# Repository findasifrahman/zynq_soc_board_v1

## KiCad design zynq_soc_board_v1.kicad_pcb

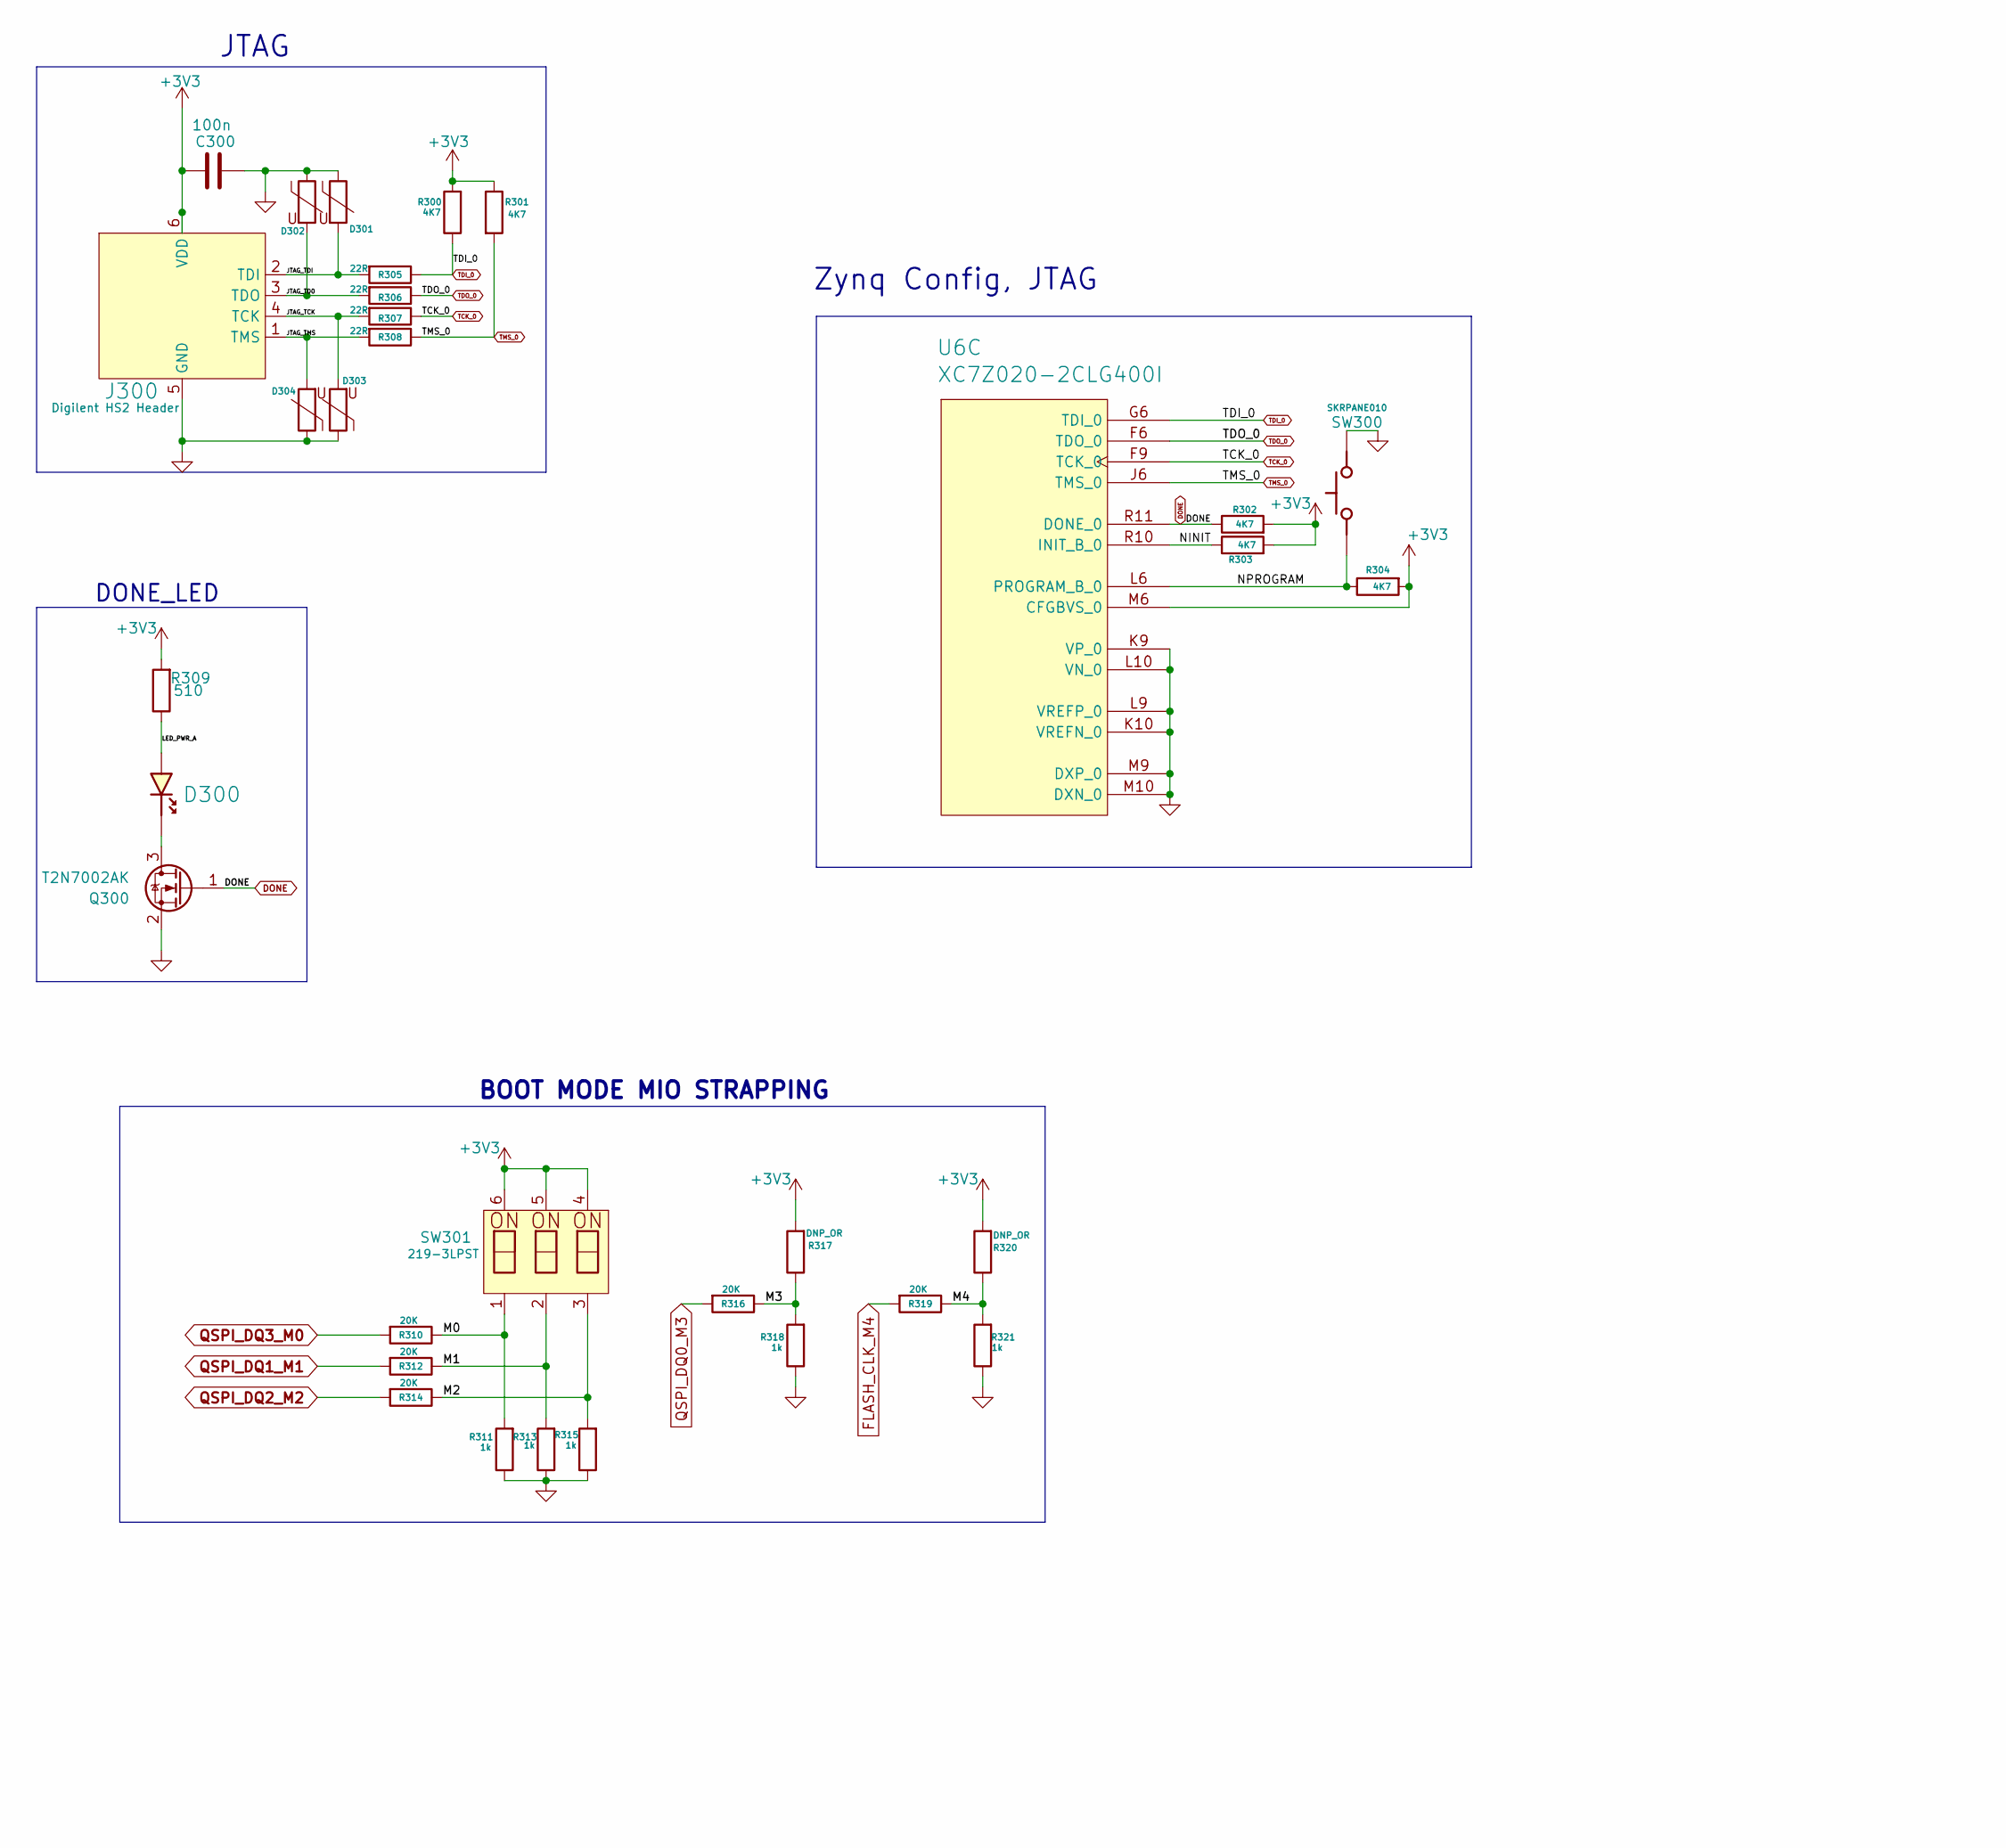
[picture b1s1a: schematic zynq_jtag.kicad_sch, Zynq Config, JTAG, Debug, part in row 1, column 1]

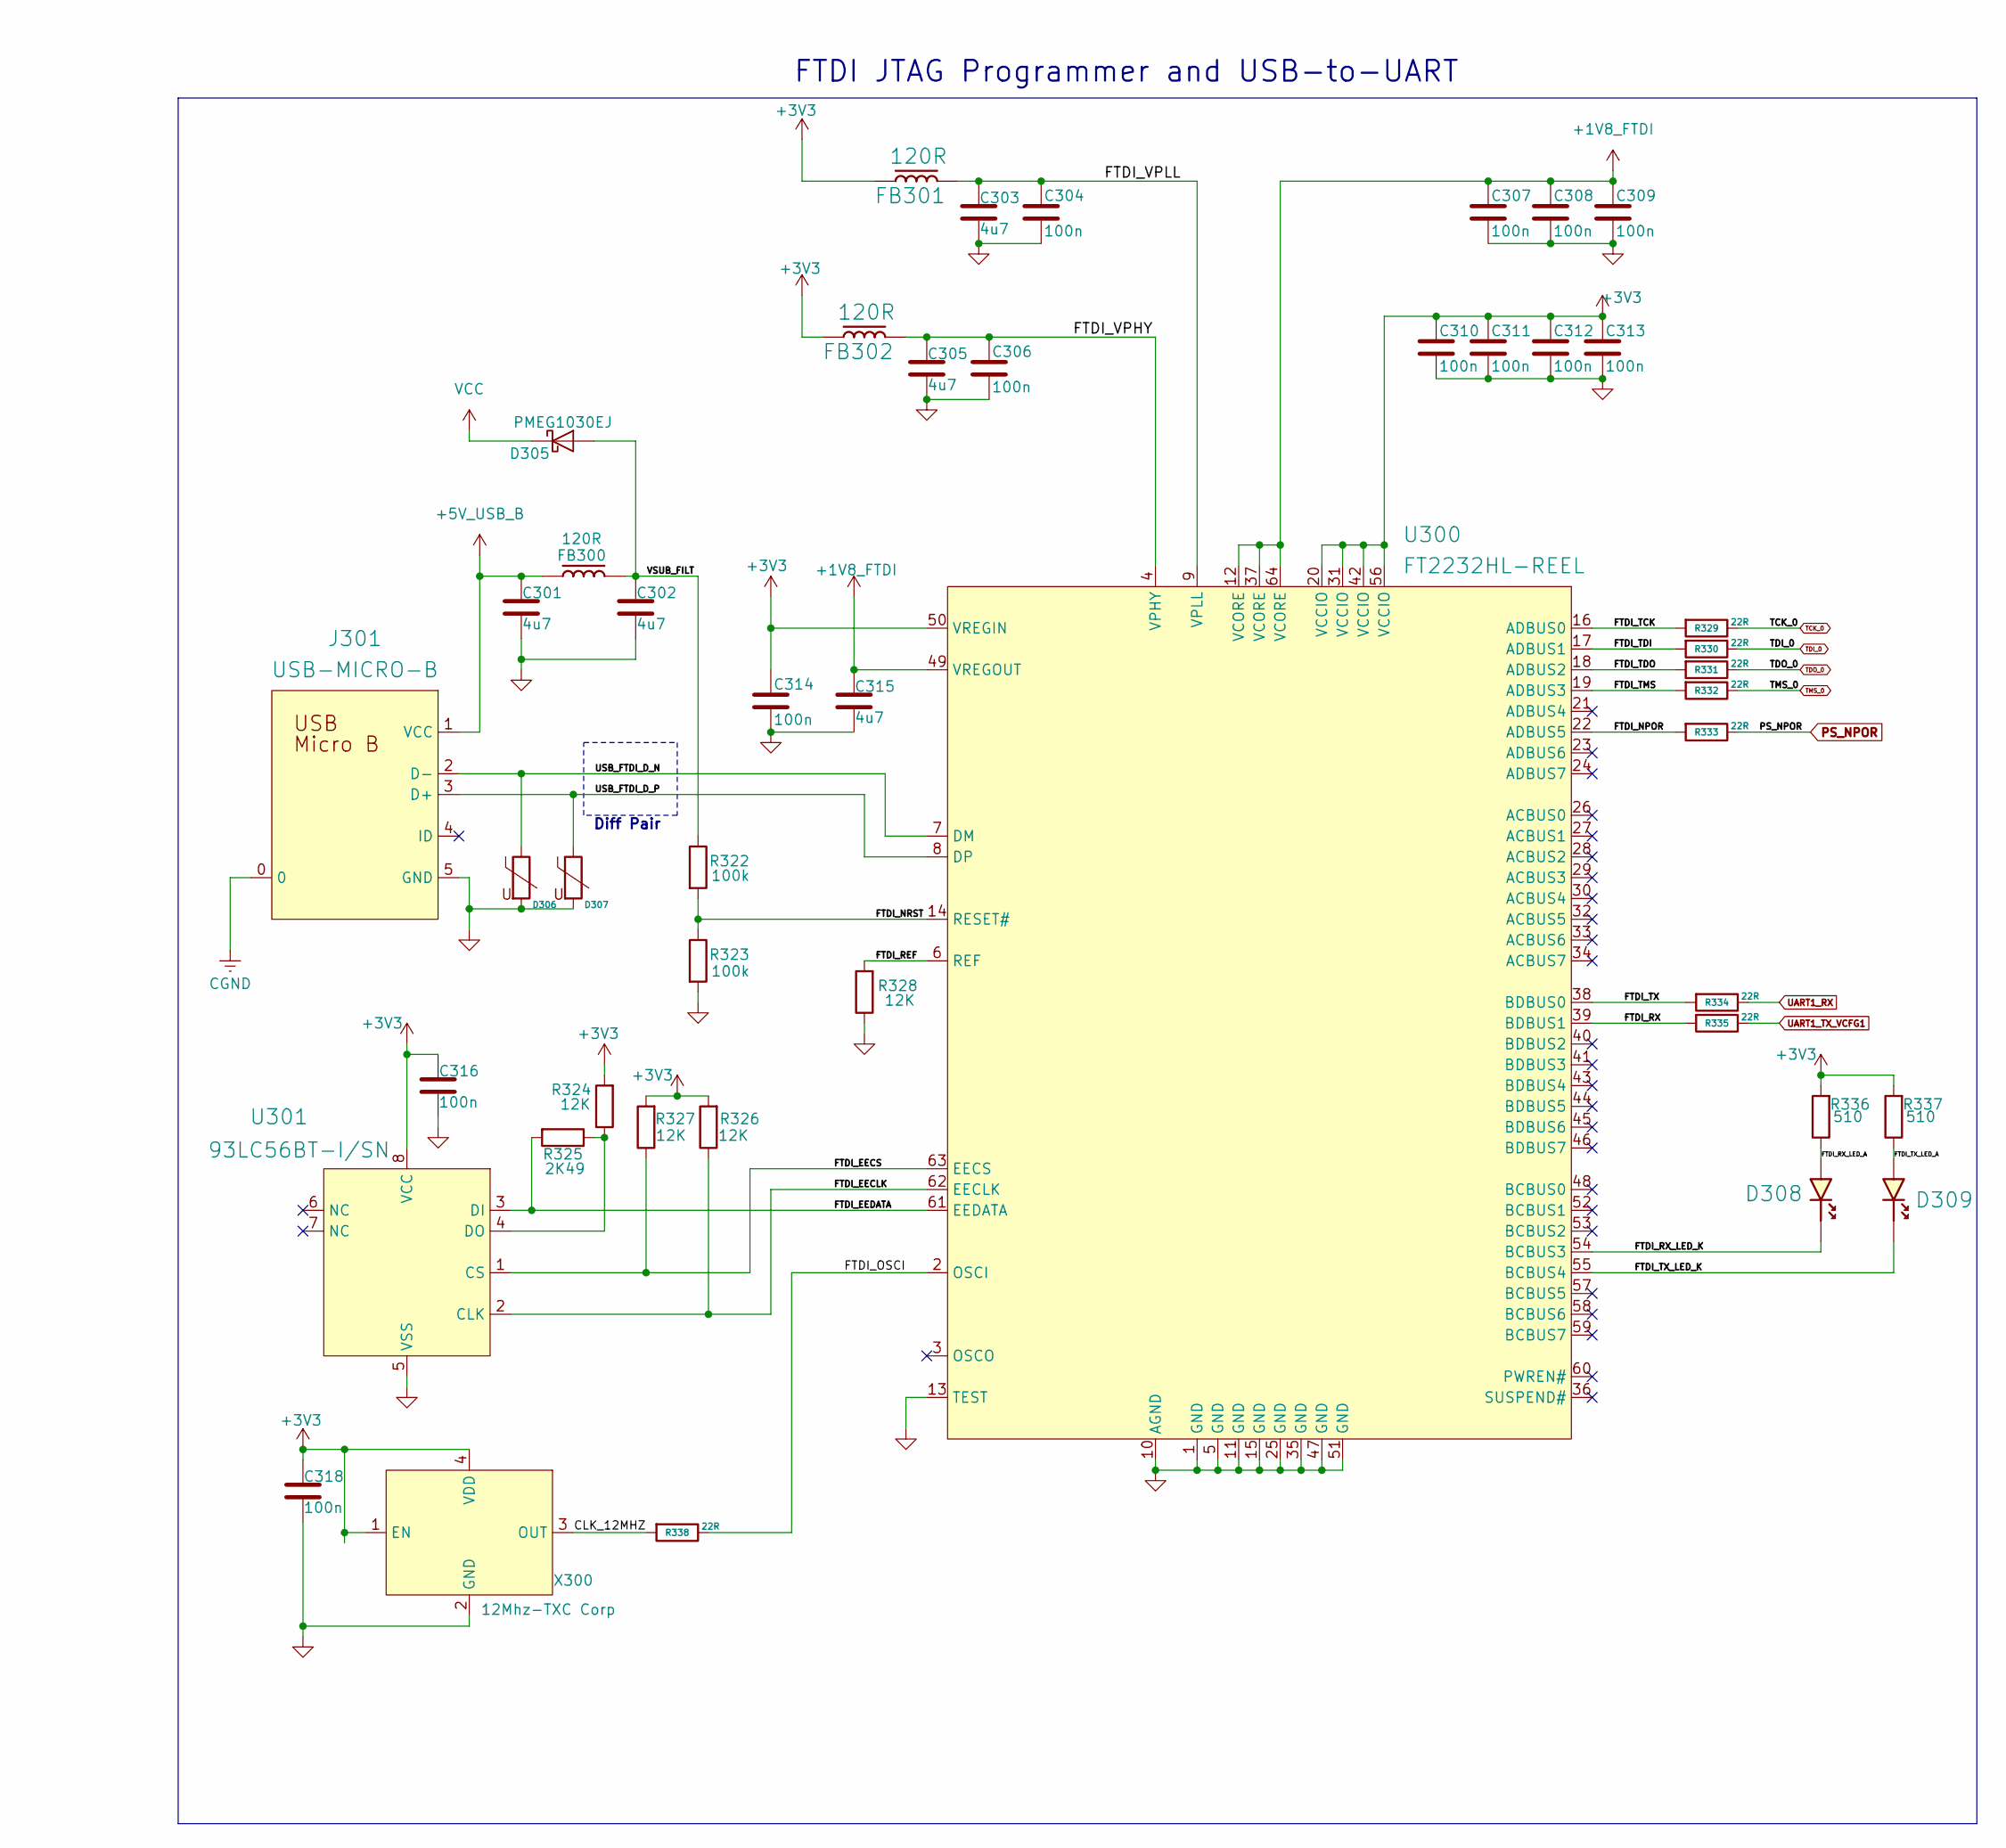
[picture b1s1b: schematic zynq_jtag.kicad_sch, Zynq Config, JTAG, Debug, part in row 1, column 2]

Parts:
C300, C304, C306, C307, C308, C309, C310, C311, C312, C313, C314, C316, C318: 100n; C_0402_1005Metric; Manufacturer Part Number CL05B104KO5NNNC; LCSC C1525
C301, C302, C303, C305, C315: 4u7; C_0402_1005Metric; Manufacturer Part Number CL05A475MP5NRNC; LCSC C23733
D300, D308, D309: RED; LED_0402_RED; Manufacturer Part Number NCD0402R1; LCSC C130719
D301, D302: Varistor; C0402; Manufacturer Part Number CG0402MLU-3.3G; LCSC C2655393
D303, D304, D306, D307: Varistor; D_0402_1005Metric; Manufacturer Part Number CG0402MLU-3.3G; LCSC C2655393
D305: PMEG1030EJ; SOD-323_L1.8-W1.3-LS2.5-RD; LCSC C133633
FB300, FB301, FB302: 120R; FB_0402; Manufacturer Part Number GZ1005D121TF; LCSC C38480
J300: Digilent HS2 Header; DIGILENT_HS2; Manufacturer Part Number 68000-406HLF; LCSC C178289
J301: USB-MICRO-B; MICRO-USB-SMD_5P-P0.65-H-M_MICRO-USB-5P; Manufacturer Part Number 920-D62A2021S10100; LCSC C40942
Q300: T2N7002AK; SOT-23; Manufacturer Part Number T2N7002AK,LM; LCSC C516175
R300, R301, R302, R303, R304: 4K7; R_0402_1005Metric; Manufacturer Part Number 0402WGF4701TCE; LCSC C25900
R305, R306, R307, R308, R329, R330, R331, R332, R333, R334, R335, R338: 22R; R_0402_1005Metric; Manufacturer Part Number 0402WGF220JTCE; LCSC C25092
R309, R336, R337: 510; R_0402_1005Metric; Manufacturer Part Number RC-02W511JT; LCSC C1119
R310, R312, R314, R316, R319: 20K; R0201; Manufacturer Part Number RC0201FR-0720KL; LCSC C295787
R311, R313, R315, R318, R321: 1k; R_0402_1005Metric; Manufacturer Part Number 0402WGF1001TCE; LCSC C11702
R317, R320: DNP_OR; R_0402_1005Metric
R322, R323: 100k; R_0402_1005Metric; Manufacturer Part Number 0402WGF1003TCE; LCSC C25741
R324, R326, R327, R328: 12K; R_0402_1005Metric; Manufacturer Part Number 0402WGF1202TCE; LCSC C25752
R325: 2K49; R_0402_1005Metric; Manufacturer Part Number 0402WGF2491TCE; LCSC C25884
SW300: SKRPANE010; Manufacturer Part Number SKRPANE010; LCSC C470426
SW301: 219-3LPST; Manufacturer Part Number 219-3LPSTR; LCSC C2961925
U6: XC7Z020-2CLG400I; Xilinx_CLG400; PartNumber XC7Z010-1CLG400C; LCSC C569043
U300: FT2232HL-REEL; LQFP-64-0.5mm; Manufacturer Part Number FT2232HL-REEL; LCSC C27882
U301: 93LC56BT-I/SN; SOIC-8; Manufacturer Part Number 93LC56B-I/SN; LCSC C183620
X300: 12Mhz-TXC Corp; XTAL_2520; Manufacturer Part Number 8W12000010; LCSC C409301

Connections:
+1V8_FTDI: C307.1, C308.1, C309.1, C315.1, U300.12 (VCORE), U300.37 (VCORE), U300.49 (VREGOUT), U300.64 (VCORE)
+3V3: C300.1, C310.1, C311.1, C312.1, C313.1, C314.1, C316.1, C318.1, FB301.1, FB302.1, J300.6 (VDD), R300.2, R301.1, R302.2, R303.2, R304.2, R309.2, R317.2, R320.2, R324.2, R326.2, R327.2, R336.2, R337.2, SW301.4, SW301.5, SW301.6, U6.M6 (CFGBVS_0), U300.20 (VCCIO), U300.31 (VCCIO), U300.42 (VCCIO), U300.50 (VREGIN), U300.56 (VCCIO), U301.8 (VCC), X300.1 (EN), X300.4 (VDD); also elsewhere on the board
+5V_USB_B: C301.1, FB300.1, J301.1 (VCC)
/zynq_jtag/CLK_12MHZ: R338.2, X300.3 (OUT)
/zynq_jtag/FTDI_EECLK: R326.1, U300.62 (EECLK), U301.2 (CLK)
/zynq_jtag/FTDI_EECS: R327.1, U300.63 (EECS), U301.1 (CS)
/zynq_jtag/FTDI_EEDATA: R325.2, U300.61 (EEDATA), U301.3 (DI)
/zynq_jtag/FTDI_NPOR: R333.2, U300.22 (ADBUS5)
/zynq_jtag/FTDI_NRST: R322.2, R323.1, U300.14 (RESET#)
/zynq_jtag/FTDI_OSCI: R338.1, U300.2 (OSCI)
/zynq_jtag/FTDI_REF: R328.2, U300.6 (REF)
/zynq_jtag/FTDI_RX: R335.2, U300.39 (BDBUS1)
/zynq_jtag/FTDI_RX_LED_A: D308.A, R336.1
/zynq_jtag/FTDI_RX_LED_K: D308.K, U300.54 (BCBUS3)
/zynq_jtag/FTDI_TCK: R329.2, U300.16 (ADBUS0)
/zynq_jtag/FTDI_TDI: R330.2, U300.17 (ADBUS1)
/zynq_jtag/FTDI_TDO: R331.2, U300.18 (ADBUS2)
/zynq_jtag/FTDI_TMS: R332.2, U300.19 (ADBUS3)
/zynq_jtag/FTDI_TX: R334.2, U300.38 (BDBUS0)
/zynq_jtag/FTDI_TX_LED_A: D309.A, R337.1
/zynq_jtag/FTDI_TX_LED_K: D309.K, U300.55 (BCBUS4)
/zynq_jtag/FTDI_VPHY: C305.1, C306.1, FB302.2, U300.4 (VPHY)
/zynq_jtag/FTDI_VPLL: C303.1, C304.1, FB301.2, U300.9 (VPLL)
/zynq_jtag/JTAG_TCK: D303.2, J300.4 (TCK), R307.2
/zynq_jtag/JTAG_TD0: D302.2, J300.3 (TDO), R306.2
/zynq_jtag/JTAG_TDI: D301.2, J300.2 (TDI), R305.2
/zynq_jtag/JTAG_TMS: D304.2, J300.1 (TMS), R308.2
/zynq_jtag/LED_PWR_A: D300.A, R309.1
/zynq_jtag/M0: R310.1, R311.2, SW301.1
/zynq_jtag/M1: R312.1, R313.2, SW301.2
/zynq_jtag/M2: R314.1, R315.2, SW301.3
/zynq_jtag/M3: R316.1, R317.1, R318.2
/zynq_jtag/M4: R319.1, R320.1, R321.2
/zynq_jtag/NINIT: R303.1, U6.R10 (INIT_B_0)
/zynq_jtag/NPROGRAM: R304.1, SW300.34, U6.L6 (PROGRAM_B_0)
/zynq_jtag/USB_FTDI_D_N: D306.1, J301.2 (D-), U300.7 (DM)
/zynq_jtag/USB_FTDI_D_P: D307.1, J301.3 (D+), U300.8 (DP)
/zynq_jtag/VSUB_FILT: C302.1, D305.2 (A), FB300.2, R322.1
CGND: J301.0; also elsewhere on the board
DONE: Q300.1 (G), R302.1, U6.R11 (DONE_0); also elsewhere on the board
FLASH_CLK_M4: R319.2
GND: C300.2, C301.2, C302.2, C303.2, C304.2, C305.2, C306.2, C307.2, C308.2, C309.2, C310.2, C311.2, C312.2, C313.2, C314.2, C315.2, C316.2, C318.2, D301.1, D302.1, D303.1, D304.1, D306.2, D307.2, J300.5 (GND), J301.5 (GND), Q300.2 (S), R311.1, R313.1, R315.1, R318.1, R321.1, R323.2, R328.1, SW300.12, U6.K9 (VP_0), U6.K10 (VREFN_0), U6.L9 (VREFP_0), U6.L10 (VN_0), U6.M9 (DXP_0), U6.M10 (DXN_0), U300.1 (GND), U300.5 (GND), U300.10 (AGND), U300.11 (GND), U300.13 (TEST), U300.15 (GND), U300.25 (GND), U300.35 (GND), U300.47 (GND), U300.51 (GND), U301.5 (VSS), X300.2 (GND); also elsewhere on the board
unnamed: D300.K, Q300.3 (D)
unnamed: R324.1, R325.1, U301.4 (DO)
PS_NPOR: R333.1; also elsewhere on the board
QSPI_DQ0_M3: R316.2; also elsewhere on the board
QSPI_DQ1_M1: R312.2; also elsewhere on the board
QSPI_DQ2_M2: R314.2; also elsewhere on the board
QSPI_DQ3_M0: R310.2; also elsewhere on the board
TCK_0: R307.1, R329.1, U6.F9 (TCK_0)
TDI_0: R300.1, R305.1, R330.1, U6.G6 (TDI_0)
TDO_0: R306.1, R331.1, U6.F6 (TDO_0)
TMS_0: R301.2, R308.1, R332.1, U6.J6 (TMS_0)
UART1_RX: R334.1; also elsewhere on the board
UART1_TX_VCFG1: R335.1; also elsewhere on the board
VCC: D305.1 (K); also elsewhere on the board

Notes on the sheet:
Diff Pair
JTAG
Zynq Config, JTAG
BOOT MODE MIO STRAPPING
FTDI JTAG Programmer and USB-to-UART
DONE_LED
